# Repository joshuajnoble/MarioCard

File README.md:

MarioCard is like MarioKart, but with Post-It notes on the floor and physical bots instead of virtual tokens on the ground. We're building the bots with Teensy boards on a 3 wheeled bot chassis with a WiFly shield to connect all of the bots to a central server. 'How do you control the phone?' you ask? With your phone of course! We'll show you schematics and other fun as we go.

The schematic is available in a Fritzing file, if you don't know what Fritzing is check it out here: http://fritzing.org/ 

You can find the WiFly library here:
https://github.com/harlequin-tech/WiFlyHQ

==========

Processing
- uses https://github.com/TooTallNate/Java-WebSocket

iOS
- uses OF and Websockets https://github.com/robotconscience/ofxLibwebsockets

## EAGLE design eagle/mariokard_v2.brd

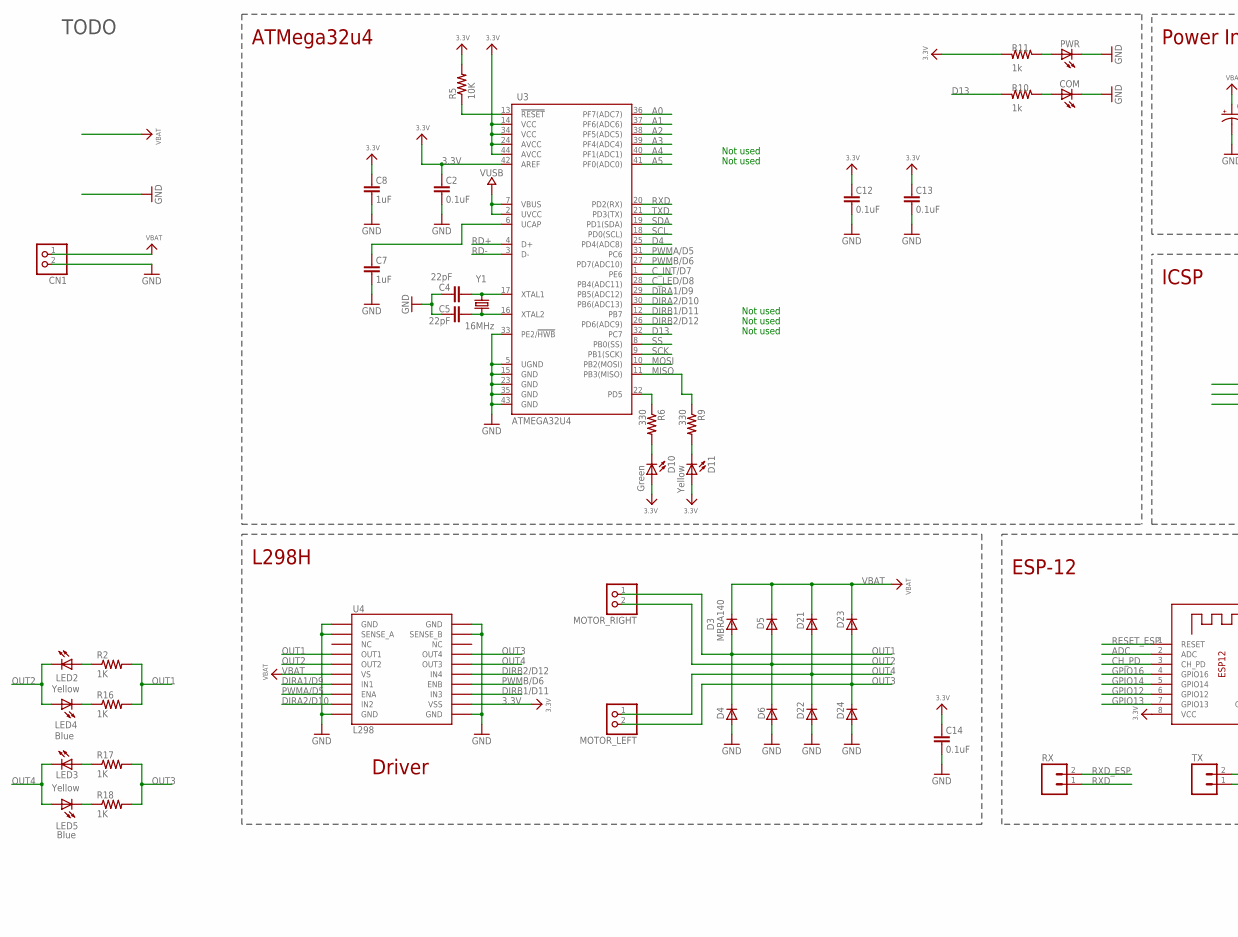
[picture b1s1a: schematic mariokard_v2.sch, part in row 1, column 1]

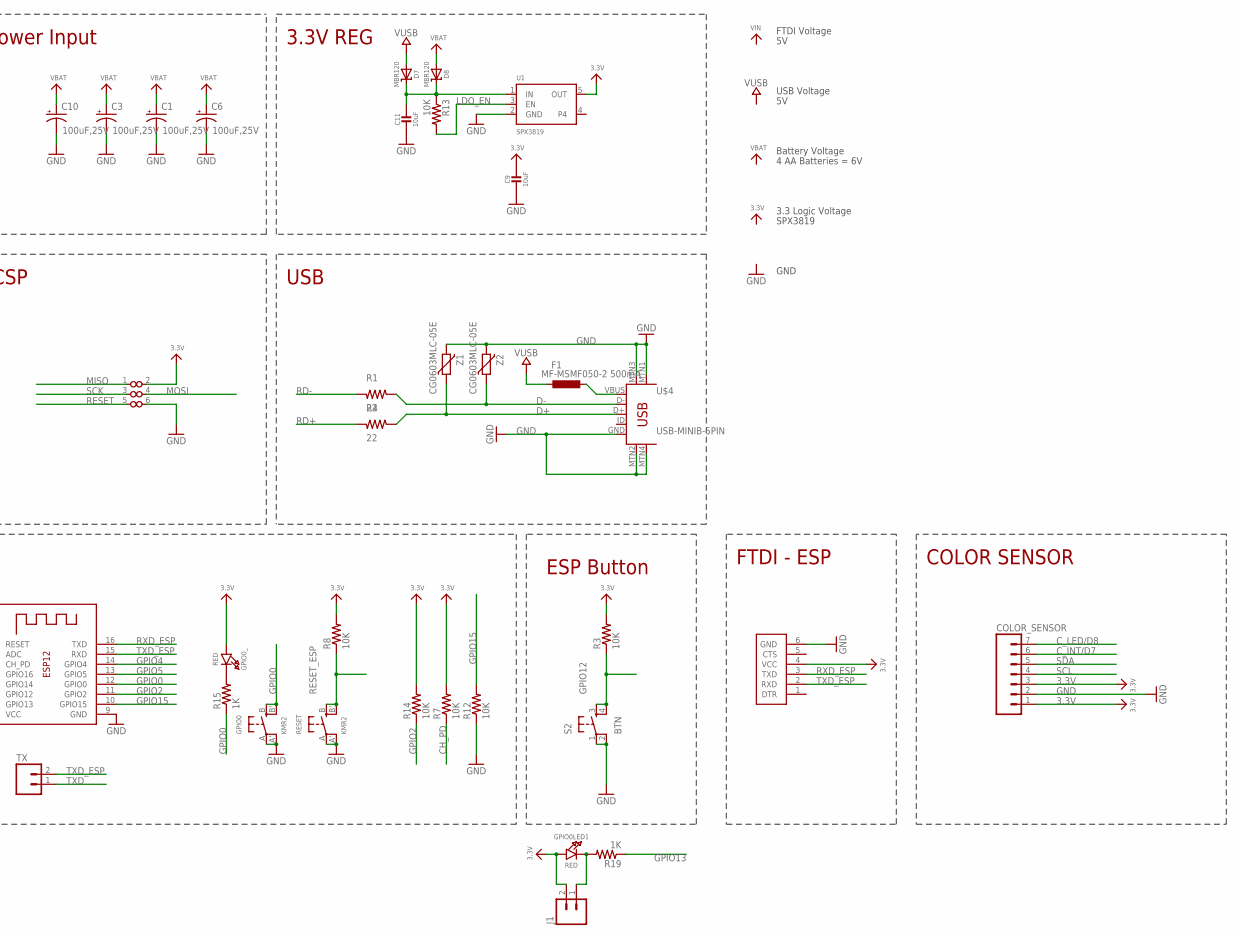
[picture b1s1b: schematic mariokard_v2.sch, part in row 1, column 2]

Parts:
C1, C3, C6, C10: 100uF,25V; NIPPON_F80
C2, C12, C13, C14: 0.1uF; 0603-CAP
C4, C5: 22pF; 0603-CAP
C7, C8: 1uF; 0603-CAP
C9, C11: 10uF; 0805-NO
CN1: JST_2PIN-THM; JST-PH-2-THM
COLOR_SENSOR: M07; 1X07
COM: LEDCHIPLED_0603; CHIPLED_0603
D3, D4, D5, D6, D21, D22, D23, D24: MBRA140; SMA-DIODE
D7, D8: MBR120; SOD-123
D10: Green; LED-0603
D11: Yellow; LED-0603
F1: MF-MSMF050-2 500mA; L1812
FTDI: FTDI_POGO
GPIO0: KMR2; BTN_KMR2_4.6X2.8
GPIO0LED1, GPIO0_: RED; CHIPLED_0805_NOOUTLINE
ISP: ISP_POGO; POGO_ISP
J1: M02PTH; 1X02
LED2, LED3: Yellow; LED-0603
LED4, LED5: Blue; LED-0603
MOTOR_LEFT: JST_2PIN-SMT-RA; JST-PH-2-SMT-RA
MOTOR_RIGHT: JST_2PIN-SMT-RA; JST-PH-2-SMT-RA
PWR: LEDCHIPLED_0603; CHIPLED_0603
R1, R4: 22; 0805
R2, R16, R17, R18: 1K; 0402-RES
R3, R7, R8, R12, R13, R14: 10K; R0603
R5: 10K; 0603-RES
R6, R9: 330; 0603-RES
R10, R11: 1k; 0805
R15, R19: 1K; R0603
RESET: KMR2; BTN_KMR2_4.6X2.8
RX: M02PTH; 1X02
S2: BTN; TACTILE-SWITCH-SMD
TX: M02PTH; 1X02
U1: SPX3819; SOT23-5
U3: ATMEGA32U4; TQFP44
U4: L298; POWERSO20
U$4: USB-MINIB-5PIN; USB-MINIB
X1: ESP-12
Y1: 16MHz; CRYSTAL-SMD-5X3
Z1, Z2: CG0603MLC-05E; CT/CN0603

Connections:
3.3V: C2.2, C8.2, C9.1, C12.2, C13.2, C14.2, COLOR_SENSOR.1, COLOR_SENSOR.3, D10.A, D11.A, FTDI.4 (VCC), GPIO0LED1.A, GPIO0_.A, ISP.2 (VCC), J1.2, R3.2, R5.2, R7.2, R8.2, R11.2, R14.2, U1.5 (OUT), U3.14 (VCC), U3.24 (AVCC), U3.34 (VCC), U3.42 (AREF), U3.44 (AVCC), U4.P$12 (VSS), X1.8 (VCC)
A0: U3.36 (PF7(ADC7))
A1: U3.37 (PF6(ADC6))
A2: U3.38 (PF5(ADC5))
A3: U3.39 (PF4(ADC4))
A4: U3.40 (PF1(ADC1))
A5: U3.41 (PF0(ADC0))
ADC: X1.2 (ADC)
CH_PD: R7.1, X1.3 (CH_PD)
C_INT/D7: COLOR_SENSOR.6, U3.1 (PE6)
C_LED/D8: COLOR_SENSOR.7, U3.28 (PB4(ADC11))
D4: U3.25 (PD4(ADC8))
D13: R10.2, U3.32 (PC7)
D+: R4.1, U$4.D+, Z1.1
D-: R1.1, U$4.D-, Z2.1
DIRA1/D9: U3.29 (PB5(ADC12)), U4.P$7 (IN1)
DIRA2/D10: U3.30 (PB6(ADC13)), U4.P$9 (IN2)
DIRB1/D11: U3.12 (PB7), U4.P$13 (IN3)
DIRB2/D12: U3.26 (PD6(ADC9)), U4.P$15 (IN4)
GND: C1.-, C2.1, C3.-, C4.2, C5.2, C6.-, C7.1, C8.1, C9.2, C10.-, C11.2, C12.1, C13.1, C14.1, CN1.2 (1), COLOR_SENSOR.2, COM.C, D4.A, D6.A, D22.A, D24.A, FTDI.6 (GND), GPIO0.A, GPIO0.A' (P1), ISP.6 (GND), PWR.C, R12.1, RESET.A, RESET.A' (P1), S2.1, S2.2, U1.2 (GND), U3.5 (UGND), U3.15 (GND), U3.23 (GND), U3.33 (PE2/!HWB), U3.35 (GND), U3.43 (GND), U4.P$1 (GND), U4.P$2 (SENSE_A), U4.P$10 (GND), U4.P$11 (GND), U4.P$19 (SENSE_B), U4.P$20 (GND), U$4.GND, U$4.MTN1 (MTN2), U$4.MTN2 (MTN3), U$4.MTN3 (MTN1), U$4.MTN4, X1.9 (GND), Z1.2, Z2.2
GPIO0: GPIO0.B (S), GPIO0.B' (S1), R15.1, X1.12 (GPIO0)
GPIO2: R14.1, X1.11 (GPIO2)
GPIO4: X1.14 (GPIO4)
GPIO5: X1.13 (GPIO5)
GPIO12: R3.1, S2.3, S2.4, X1.6 (GPIO12)
GPIO13: R19.1, X1.7 (GPIO13)
GPIO14: X1.5 (GPIO14)
GPIO15: R12.2, X1.10 (GPIO15)
GPIO16: X1.4 (GPIO16)
LDO_EN: R13.2, U1.3 (EN)
MISO: ISP.1 (MISO), R9.1, U3.11 (PB3(MISO))
MOSI: ISP.4 (MOSI), U3.10 (PB2(MOSI))
unnamed: C5.1, U3.16 (XTAL2), Y1.1
unnamed: C4.1, U3.17 (XTAL1), Y1.3 (2)
unnamed: C7.2, U3.6 (UCAP)
unnamed: C11.1, D7.C, D8.C, R13.1, U1.1 (IN)
unnamed: LED2.A, R2.1
unnamed: LED4.C, R16.1
unnamed: LED5.C, R18.1
unnamed: LED3.A, R17.1
unnamed: COM.A, R10.1
unnamed: PWR.A, R11.1
unnamed: GPIO0_.C, R15.2
unnamed: F1.1, U$4.VBUS
unnamed: D11.C, R9.2
unnamed: D10.C, R6.2
unnamed: GPIO0LED1.C, J1.1, R19.2
OUT1: D3.A, D4.C, MOTOR_RIGHT.1 (2), R2.2, R16.2, U4.P$4 (OUT1)
OUT2: D5.A, D6.C, LED2.C, LED4.A, MOTOR_RIGHT.2 (1), U4.P$5 (OUT2)
OUT3: D23.A, D24.C, MOTOR_LEFT.2 (1), R17.2, R18.2, U4.P$17 (OUT4)
OUT4: D21.A, D22.C, LED3.C, LED5.A, MOTOR_LEFT.1 (2), U4.P$16 (OUT3)
PWMA/D5: U3.31 (PC6), U4.P$8 (ENA)
PWMB/D6: U3.27 (PD7(ADC10)), U4.P$14 (ENB)
RD+: R4.2, U3.4 (D+)
RD-: R1.2, U3.3 (D-)
RESET: ISP.5 (RESET), R5.1, U3.13 (!RESET)
RESET_ESP: R8.1, RESET.B (S), RESET.B' (S1), X1.1 (RESET)
RXD: RX.1, U3.20 (PD2(RX))
RXD_ESP: FTDI.3 (TXD), RX.2, X1.16 (TXD)
SCK: ISP.3 (SCK), U3.9 (PB1(SCK))
SCL: COLOR_SENSOR.4, U3.18 (PD0(SCL))
SDA: COLOR_SENSOR.5, U3.19 (PD1(SDA))
SS: U3.8 (PB0(SS))
TXD: TX.1, U3.21 (PD3(TX))
TXD_ESP: FTDI.2 (RXD), TX.2, X1.15 (RXD)
TXLED1: R6.1, U3.22 (PD5)
VBAT: C1.+, C3.+, C6.+, C10.+, CN1.1 (2), D3.C, D5.C, D8.A, D21.C, D23.C, U4.P$6 (VS)
VUSB: D7.A, F1.2, U3.2 (UVCC), U3.7 (VBUS)

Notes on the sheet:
3.3V REG
USB
ICSP
ATMega32u4
ESP-12
FTDI - ESP
L298H
Not used
Power Input
TODO
FTDI Voltage
USB Voltage
Battery Voltage
3.3 Logic Voltage
GND
4 AA Batteries = 6V
SPX3819
Driver
COLOR SENSOR
ESP Button

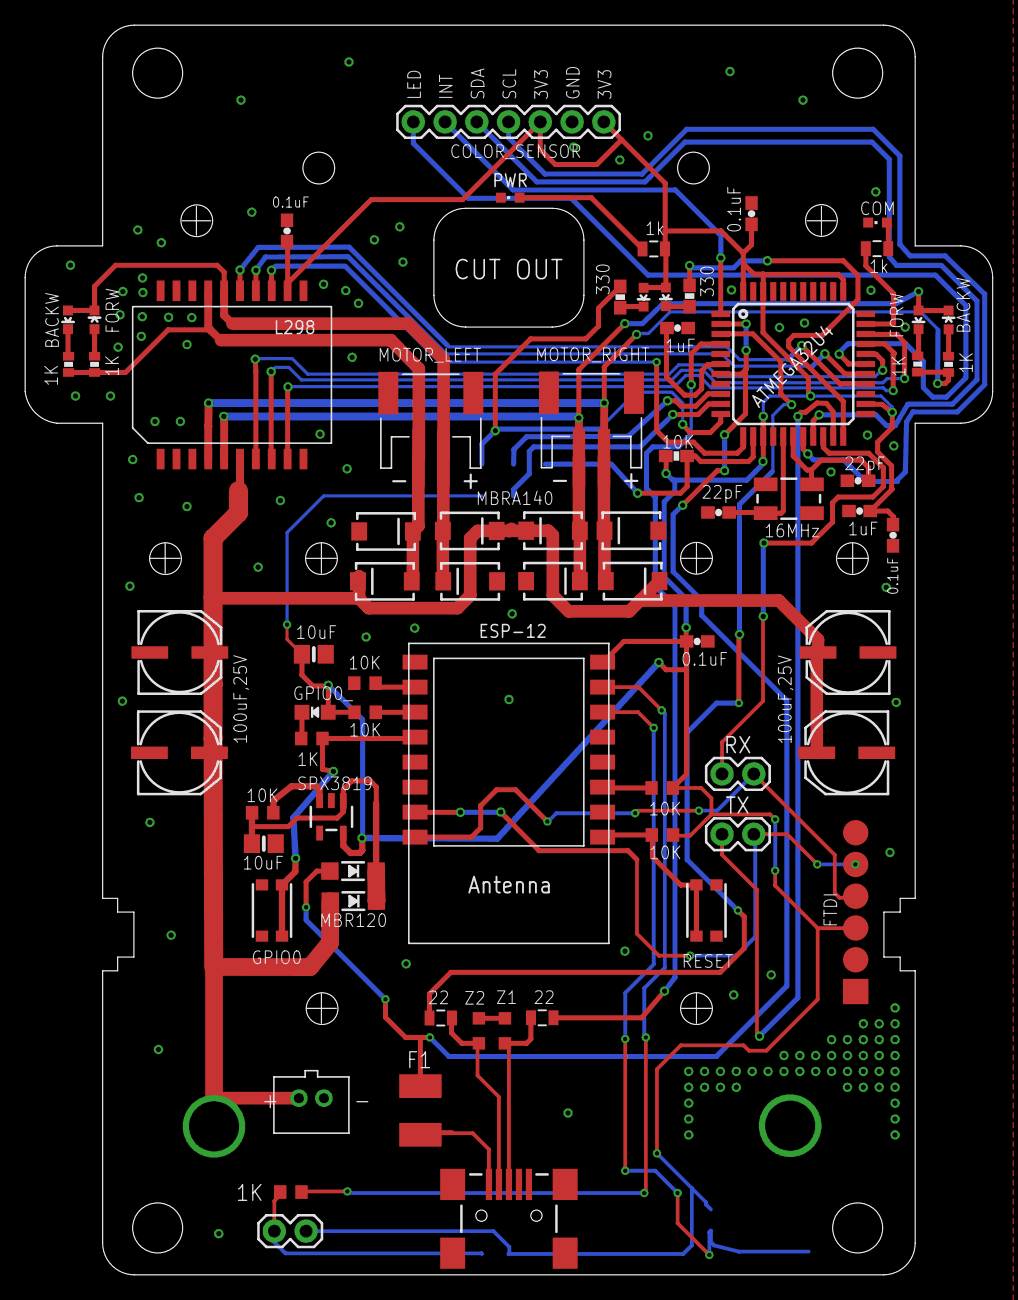
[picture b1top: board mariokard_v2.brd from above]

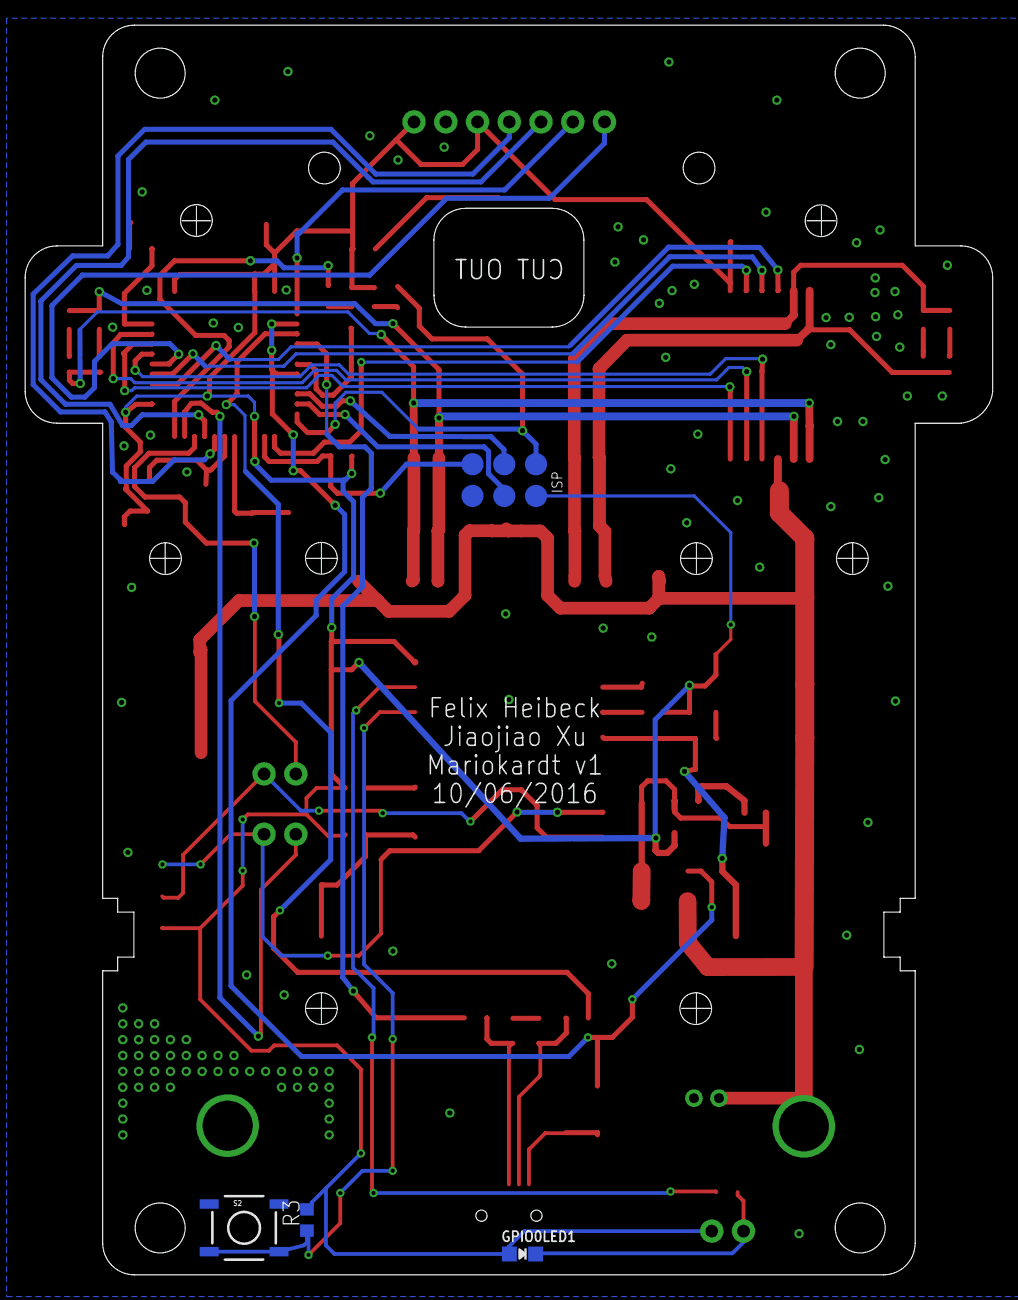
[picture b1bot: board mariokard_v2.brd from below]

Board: 2 copper layers, 77.4 x 100.0 mm, 74 parts (4 on the bottom side), 55 nets.

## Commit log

2012-12-19 initial commit to new repo
2012-12-21 adding sensor fusion to ios app
2012-12-21 making MarioKardApp mm instead of cpp for CoreMotion
2012-12-22 updating iphone steering
2013-04-12 fixing up iOS app
2013-04-12 quick bug in turning left
2013-04-13 updating arduino app and server for color sending/receiving
2013-04-14 fixing up server for iOS
2013-04-17 updating iOS app
2013-04-21 cleaning up color detection, server still needs work
2013-04-25 fixing an error in the python server
2016-07-27 updating to OF
2016-07-31 made nice-ish road
2016-07-31 updating server & client
2016-07-31 quick code update for winc
2016-08-04 udp not websockets
2016-08-04 include ofxnetwork
2016-08-08 adding esp sketch
2016-08-09 at328 client update
2016-08-15 adding esp12
2016-09-07 adding of android app
2016-10-03 lots of updates
2016-10-03 classic python indent erorr
2016-10-03 port number
2016-10-03 str split
2016-10-03 adding test client
2016-10-03 port change
2016-10-05 board tested and working
2016-10-05 cart testing
2016-10-05 android update
2016-10-05 adding android
2016-10-05 dead files
2016-10-05 remove jars
2016-10-05 adding eagle
2016-10-05 update gitignore
2016-10-05 better?
2016-10-05 more bfg
2016-10-05 more gitignore
2016-10-05 remove android
2016-10-05 rm-ing
2016-10-05 accidental add
2016-10-11 server updates
2016-10-11 threads?
2016-10-11 updating keep alive
2016-10-11 I wrote bad code
2016-10-11 minor server updates
2016-10-11 better class
2016-10-11 more pyclass
2016-10-12 adding some testing capacity
2016-10-12 test sever
2016-10-12 typo
2016-10-12 server changes
2016-10-13 server send next
2016-10-13 better send
2016-10-13 whateve
2016-10-16 adding felix new board
2016-10-17 server tweaking
2016-10-17 better exit
2016-10-18 arduino sends colors always
2016-10-18 server color handle
2016-10-18 lots of server updates
2016-10-18 rlock
2016-10-18 prune empty events
2016-10-18 server munge
2016-10-18 server still broken threading
2016-10-19 indent error
2016-10-25 adding tcp server
2016-10-25 tcp for esp too
2016-10-26 cleaning up tcp
2016-10-27 tcp better
2016-10-27 saving local
2016-10-28 typo in event handling
2016-11-02 tracking down cart errors
2016-12-02 got a functional android app
2017-02-21 updating server
2017-02-21 update the arduinos
2017-02-21 server updating

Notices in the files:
parts and their libraries:
SparkFun-Connectors: Licensing: Creative Commons ShareAlike 4.0 International - https://creativecommons.org/licenses/by-sa/4.0
microbuilder: This work is placed in the public domain, and may be freely used for commercial and non-commercial work with the following conditions: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
